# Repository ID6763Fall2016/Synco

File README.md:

# Team Synco

## Authors

* Diego Osorio
* Shambhavi Mahajan

Monitors traffic and directions on stairs

[Stairs Monitor](./project-stairs/README.md)
[Transit Notifier](./transit-notifier/README.md)

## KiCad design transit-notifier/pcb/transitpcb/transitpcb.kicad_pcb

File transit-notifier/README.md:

# Team Synco - Transit Notifier

Monitors traffic and directions on stairs

[Blog](http://ipdl.gatech.edu/doie2016/projects/5synco-transit-notifier/)

This folder holds the source code of the Stairs Monitor.

## Authors

* Diego Osorio
* Shambhavi Mahajan

## System

* Components
  *	[Adafruit Huzzah ESP8266 Breakout](https://www.adafruit.com/product/2471)
  * 2 x 8-Channel Capacitive Touch Sensor Breakout [Adafruit CAP1188](https://www.adafruit.com/products/1602)
  * 2 x 14 Leds [Adafruit NeoPixel RGB Led strip](https://www.adafruit.com/products/1460)
  * 25 leds [Adafruit RGB Led pixels](https://www.adafruit.com/products/322)

* Input
  * 16 x Capacitive touch channels
  * GTBus Api services

* Output
  * Stop array using RBG led Pixels
  * Waiting time using Neo Pixel strip
  * Bus route display using Neo Pixel strip

## Libraries

The following libraries are needed:

### Arduino libraries

* [Adafruit Huzzah ESP8266 Breakout - ESP8266](https://github.com/esp8266/Arduino)
* [Adafruit RGB Led pixels - WS2801](https://github.com/adafruit/Adafruit-WS2801-Library)
* [Adafruit NeoPixel RGB Led strip - DotStar](https://github.com/adafruit/Adafruit_DotStar)
* [8-Channel Capacitive Touch Sensor Breakout - CAP1188](https://github.com/adafruit/Adafruit_CAP1188_Library)

### tinyxml2

Handle XML loading and parsing

* [Reference](http://www.grinninglizard.com/tinyxml2/)
* [Library](https://github.com/leethomason/tinyxml2)

### Fritzing Adafruit Library

* [Fritzing Adafruit Library](https://github.com/adafruit/Fritzing-Library)

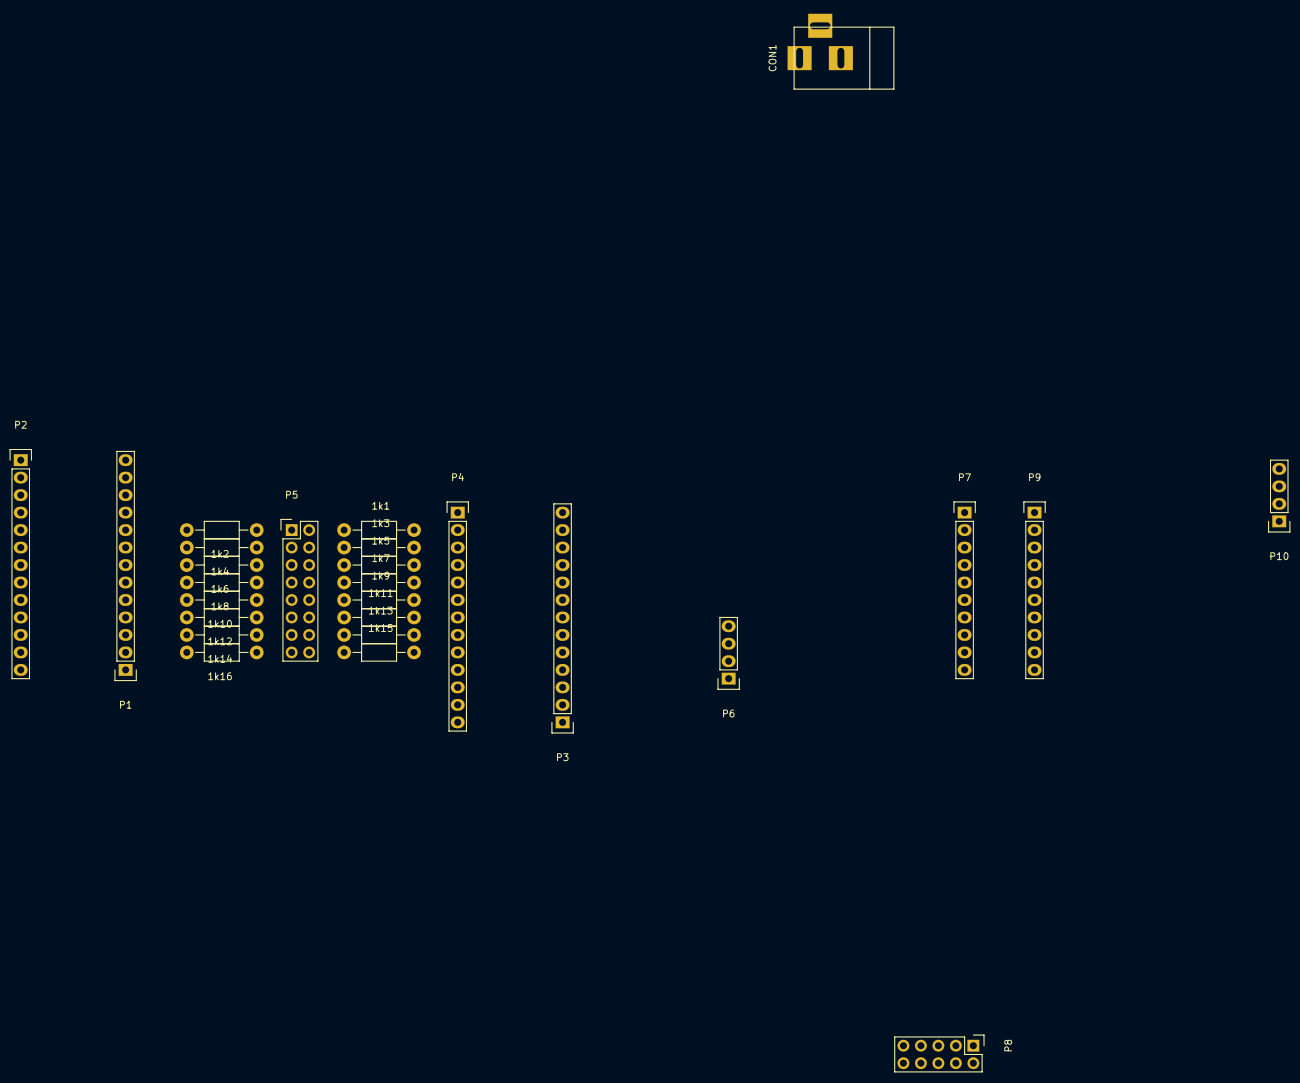
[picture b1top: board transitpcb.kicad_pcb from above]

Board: 2 copper layers, 27 parts (0 on the bottom side), 46 nets, no tracks yet.

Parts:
1k1, 1k2, 1k3, 1k4, 1k5, 1k6, 1k7, 1k8, 1k9, 1k10, 1k11, 1k12, 1k13, 1k14, 1k15, 1k16: R; Resistor_Horizontal_RM10mm
CON1: BARREL_JACK
P1, P2, P3, P4: CONN_01X13; Pin_Header_Straight_1x13
P5: CONN_02X08; Pin_Header_Straight_2x08
P6: CONN_01X02; Pin_Header_Straight_1x04
P7, P9: CONN_01X10; Pin_Header_Straight_1x10
P8: CONN_02X05; Pin_Header_Straight_2x05
P10: CONN_01X04; Pin_Header_Straight_1x04

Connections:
C1: 1k2.2, P1.9
C2: 1k4.2, P1.8
C3: 1k6.2, P1.7
C4: 1k8.2, P1.6
C5: 1k10.2, P1.5
C6: 1k12.2, P1.4
C7: 1k14.2, P1.3
C8: 1k16.2, P1.2
C9: 1k15.2, P4.9
C10: 1k13.2, P4.8
C11: 1k11.2, P4.7
C12: 1k9.2, P4.6
C13: 1k7.2, P4.5
C14: 1k5.2, P4.4
C15: 1k3.2, P4.3
C16: 1k1.2, P4.2
GND: CON1.2, P2.4, P3.4, P8.2, P8.3, P8.4, P9.1, P10.4
unnamed: 1k1.1, P5.2
unnamed: 1k2.1, P5.1
unnamed: 1k3.1, P5.4
unnamed: 1k4.1, P5.3
unnamed: 1k5.1, P5.6
unnamed: 1k6.1, P5.5
unnamed: 1k7.1, P5.8
unnamed: 1k8.1, P5.7
unnamed: 1k9.1, P5.10
unnamed: 1k10.1, P5.9
unnamed: 1k11.1, P5.12
unnamed: 1k12.1, P5.11
unnamed: 1k13.1, P5.14
unnamed: 1k14.1, P5.13
unnamed: 1k15.1, P5.16
unnamed: 1k16.1, P5.15
RX: P6.2, P7.9
Reset: P8.1, P9.10
RouteData: P8.6, P9.7
RouteSCK: P8.8, P9.6
SCK: P2.2, P3.2, P7.8
SDA: P2.1, P3.1, P7.7
StopsData: P9.4, P10.3
StopsSCK: P9.5, P10.2
TX: P6.1, P7.10
TimeData: P7.4, P8.5
TimeSCK: P7.5, P8.7
V33: P1.1, P1.10
VIN: CON1.1, P2.3, P3.3, P8.9, P8.10, P9.2, P10.1

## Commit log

2016-09-13 Node.js tutorials
2016-09-15 Add Motion sensor test project
2016-09-16 Project servo test
2016-09-16 Project servo web page
2016-09-16 Updating servo movement
2016-09-20 Project Alive
2016-09-20 Alive update logs
2016-09-20 Project stairs
2016-09-21 versioning data-base
2016-09-21 Store ultrasonic values
2016-09-21 Setup time for ultrasonic sensor
2016-09-22 Updated database
2016-09-22 Charting
2016-09-22 page update
2016-09-29 Update interfase
2016-09-29 Command arguments
2016-09-29 Add socket.io
2016-09-29 Code comments
2016-10-12 Move blog link
2016-11-02 Transit notifier
2016-11-02 Adding read me files
2016-11-02 Update blog url
2016-11-02 Adding lasercut and stiut and stickers files
